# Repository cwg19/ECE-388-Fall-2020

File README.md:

# Function Generator
## UMassD ECE 388 Embedded System Design

### Project Scope
Simple Function gnerator
* produces sinusoid, square, and triangle waves
* Adjustable frequency up to 1MHz
* Adjustable gain between +/- ~10V
* Adjustable phase
* Rotary encoder w/ push button to select setting and change value
* Keypad to enter value
* LCD display

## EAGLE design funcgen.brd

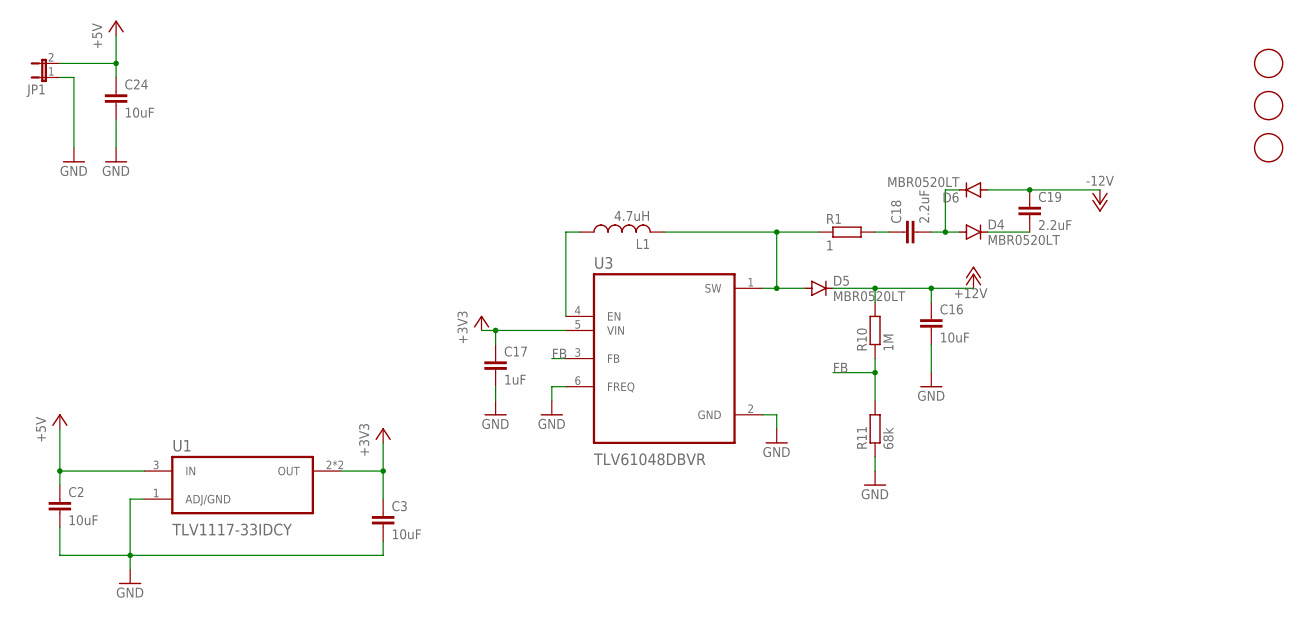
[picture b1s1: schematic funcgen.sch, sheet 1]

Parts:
C2, C3, C16, C24: 10uF; C0805
C17: 1uF; C0805
C18, C19: 2.2uF; C0805
D4, D5, D6: MBR0520LT; SOD123
JP1: JP1E; JP1
L1: 4.7uH; C0805
R1: 1; R0805
R10: 1M; R0805
R11: 68k; R0805
U1: TLV1117-33IDCY; SOT230P700X180-4N
U3: TLV61048DBVR; SOT95P280X145-6N
U$1, U$3, U$4: FIDUCIAL; FIDUCIAL_1MM

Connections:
+3V3: C3.1, C17.1, U1.2 (OUT), U1.4 (OUT), U3.5 (VIN); also elsewhere on the board
+5V: C2.1, C24.1, JP1.2, U1.3 (IN); also elsewhere on the board
+12V: C16.1, D5.C, R10.2; also elsewhere on the board
-12V: C19.1, D6.A; also elsewhere on the board
FB: R10.1, R11.2, U3.3 (FB)
GND: C2.2, C3.2, C16.2, C17.2, C24.2, JP1.1, R11.1, U1.1 (ADJ/GND), U3.2 (GND), U3.6 (FREQ); also elsewhere on the board
unnamed: L1.1, U3.4 (EN)
unnamed: D5.A, L1.2, R1.1, U3.1 (SW)
unnamed: C18.1, R1.2
unnamed: C18.2, D4.A, D6.C
unnamed: C19.2, D4.C

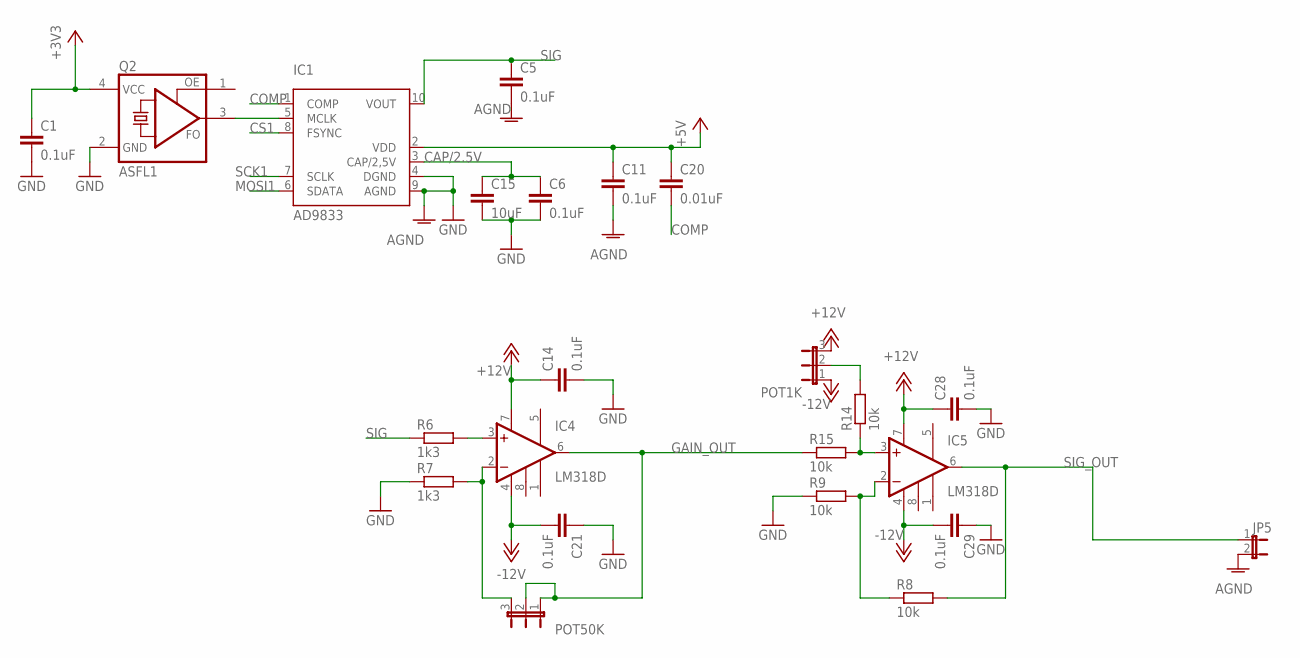
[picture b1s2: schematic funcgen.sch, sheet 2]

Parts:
C1, C5, C6, C11, C14, C21, C28, C29: 0.1uF; C0805
C15: 10uF; C0805
C20: 0.01uF; C0805
IC1: AD9833; MSOP10
IC4, IC5: LM318D; SOIC8
JP5: JP1E; JP1
POT1K, POT50K: JP2E; JP2
Q2: ASFL1; ASF
R6, R7: 1k3; R0805
R8, R9, R14, R15: 10k; R0805

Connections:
+3V3: C1.1, Q2.4 (VCC); also elsewhere on the board
+5V: C11.1, C20.1, IC1.2 (VDD); also elsewhere on the board
+12V: C14.1, C28.1, IC4.7 (V+), IC5.7 (V+), POT1K.3; also elsewhere on the board
-12V: C21.2, C29.2, IC4.4 (V-), IC5.4 (V-), POT1K.1; also elsewhere on the board
AGND: C5.2, C11.2, IC1.4 (DGND), IC1.9 (AGND), JP5.2
CAP/2.5V: C6.1, C15.1, IC1.3 (CAP/2,5V)
COMP: C20.2, IC1.1 (COMP)
CS1: IC1.8 (FSYNC); also elsewhere on the board
GAIN_OUT: IC4.6 (OUT), POT50K.1, POT50K.2, R15.1
GND: C1.2, C6.2, C14.2, C15.2, C21.1, C28.2, C29.1, Q2.2 (GND), R7.1, R9.1; also elsewhere on the board
MOSI1: IC1.6 (SDATA); also elsewhere on the board
unnamed: IC1.5 (MCLK), Q2.3 (FO)
unnamed: IC4.3 (+IN), R6.2
unnamed: IC4.2 (-IN), POT50K.3, R7.2
unnamed: IC5.3 (+IN), R14.1, R15.2
unnamed: POT1K.2, R14.2
unnamed: IC5.2 (-IN), R8.1, R9.2
SCK1: IC1.7 (SCLK); also elsewhere on the board
SIG: C5.1, IC1.10 (VOUT), R6.1
SIG_OUT: IC5.6 (OUT), JP5.1, R8.2

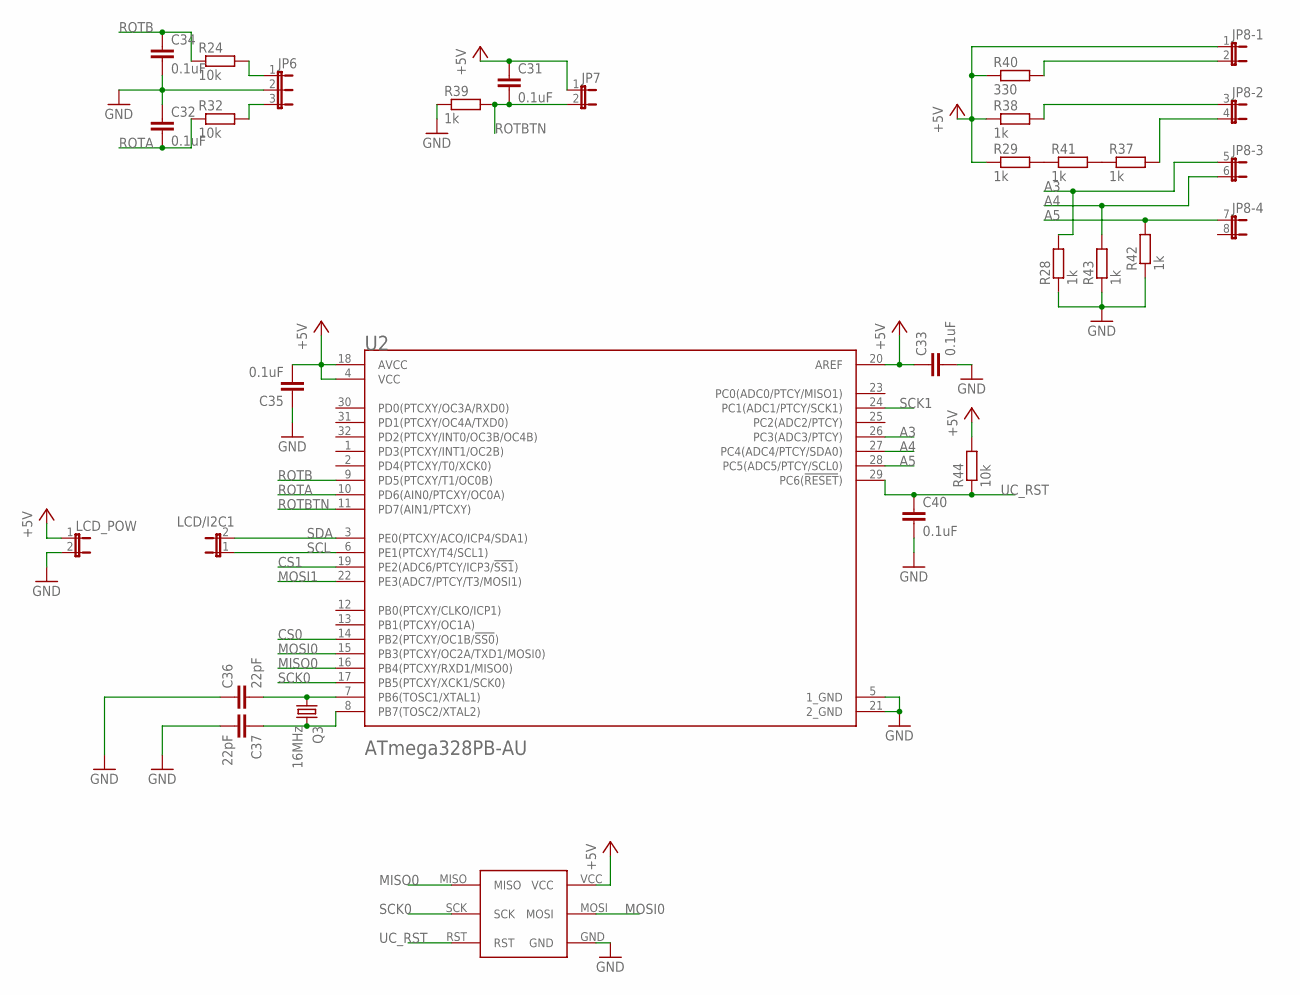
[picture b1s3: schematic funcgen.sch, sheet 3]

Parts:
C31, C32, C33, C34, C35, C40: 0.1uF; C0805
C36, C37: 22pF; C0805
JP6: JP2E; JP2
JP7: JP1E; JP1
JP8: JP4QE; JP4Q
LCD/I2C1: JP1E; JP1
LCD_POW: JP1E; JP1
Q3: 16MHz; HC49UP
R24, R32, R44: 10k; R0805
R28, R29, R37, R38, R39, R41, R42, R43: 1k; R0805
R40: 330; R0805
U2: MICROCHIP_ATMEGA328PB-AUMICROCHIP_ATMEGA328PB-AU_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; MICROCHIP_ATMEGA328PB-AU_0
U$2: AVR-ISP

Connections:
+5V: C31.1, C33.1, C35.2, JP7.1, JP8.1, LCD_POW.1, R29.1, R38.1, R40.1, R44.2, U2.4 (VCC), U2.18 (AVCC), U2.20 (AREF), U$2.VCC; also elsewhere on the board
A3: JP8.5 (1), R28.2, U2.26 (PC3(ADC3/PTCY))
A4: JP8.6 (2), R43.2, U2.27 (PC4(ADC4/PTCY/SDA0))
A5: JP8.7 (1), R42.2, U2.28 (PC5(ADC5/PTCY/SCL0))
CS0: U2.14 (PB2(PTCXY/OC1B/!SS0!))
CS1: U2.19 (PE2(ADC6/PTCY/ICP3/!SS1!)); also elsewhere on the board
GND: C32.1, C33.2, C34.2, C35.1, C36.1, C37.2, C40.2, JP6.2, LCD_POW.2, R28.1, R39.1, R42.1, R43.1, U2.5 (1_GND), U2.21 (2_GND), U$2.GND; also elsewhere on the board
MISO0: U2.16 (PB4(PTCXY/RXD1/MISO0)), U$2.MISO
MOSI0: U2.15 (PB3(PTCXY/OC2A/TXD1/MOSI0)), U$2.MOSI
MOSI1: U2.22 (PE3(ADC7/PTCY/T3/MOSI1)); also elsewhere on the board
unnamed: JP6.1, R24.2
unnamed: JP6.3, R32.2
unnamed: C36.2, Q3.1, U2.7 (PB6(TOSC1/XTAL1))
unnamed: C37.1, Q3.2, U2.8 (PB7(TOSC2/XTAL2))
unnamed: R37.1, R41.2
unnamed: R29.2, R41.1
unnamed: JP8.2, R40.2
unnamed: JP8.3 (1), R38.2
unnamed: JP8.4 (2), R37.2
ROTA: C32.2, R32.1, U2.10 (PD6(AIN0/PTCXY/OC0A))
ROTB: C34.1, R24.1, U2.9 (PD5(PTCXY/T1/OC0B))
ROTBTN: C31.2, JP7.2, R39.2, U2.11 (PD7(AIN1/PTCXY))
SCK0: U2.17 (PB5(PTCXY/XCK1/SCK0)), U$2.SCK
SCK1: U2.24 (PC1(ADC1/PTCY/SCK1)); also elsewhere on the board
SCL: LCD/I2C1.1, U2.6 (PE1(PTCXY/T4/SCL1))
SDA: LCD/I2C1.2, U2.3 (PE0(PTCXY/ACO/ICP4/SDA1))
UC_RST: C40.1, R44.1, U2.29 (PC6(!RESET!)), U$2.RST

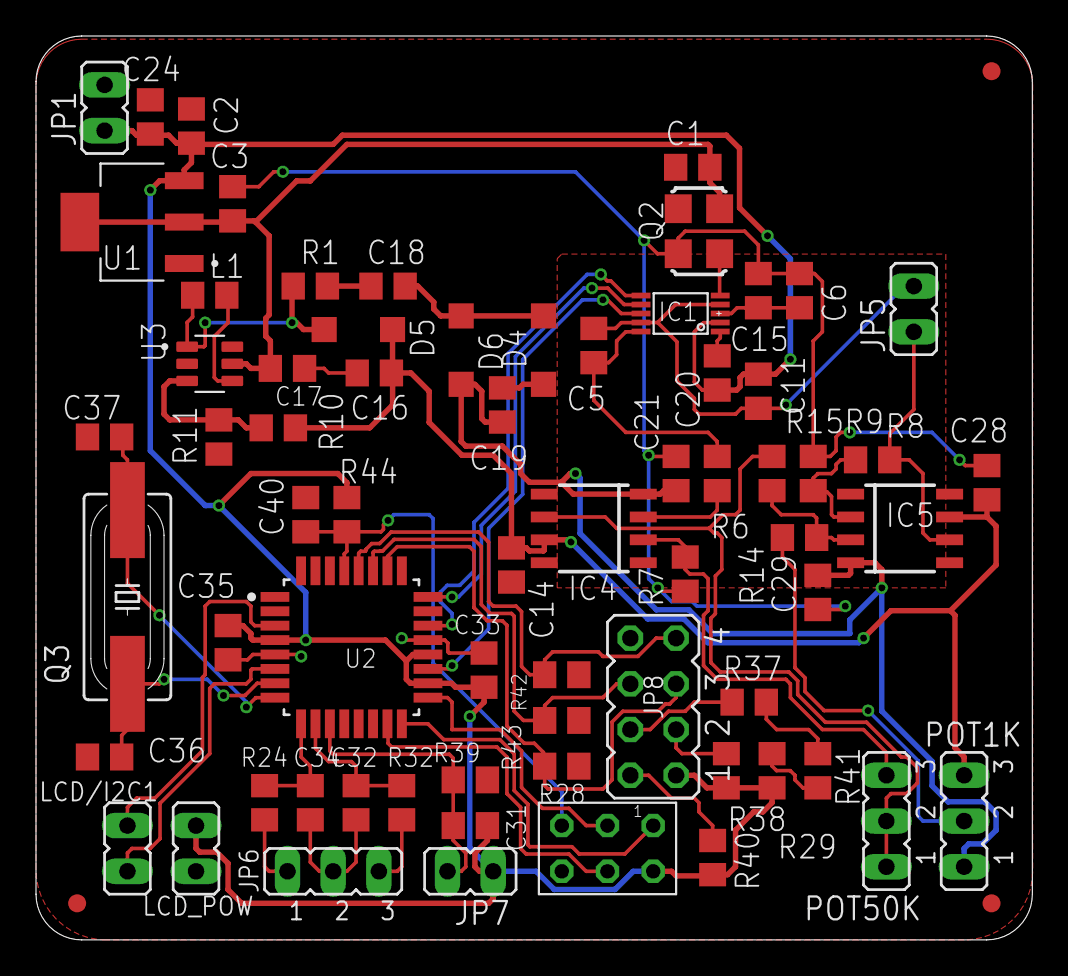
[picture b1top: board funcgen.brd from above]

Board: 2 copper layers, 55.4 x 50.2 mm, 71 parts (0 on the bottom side), 47 nets.

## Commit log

2020-10-11 Initial software upload
2020-10-11 Bill of Materials
    Revised Bill of Materials submission with information on parts from LCSC and digikey depending on availability.
    I left resistors and capacitors blank except for the component value because we are all supposed to be using the 0805 components. I did not fill out LEDs because I do not need any particular LEDs. Co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
2020-10-12 Updating UI solution
    Rotary encoder interfacing is successful. Have yet to separate functionality into header and implementation files for lcd and rotary encoder functionality. The main program of this project is a test,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
2020-10-12 Functional user Interface program
    UI code with 4x20 LCD and I2C backpack. Works well despite sometimes skipping modes when rotating encoder and sometimes missing button pushes. I tried incorporating a timer to check the push button a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
2020-10-12 .csv BOM
2020-10-13 Create BOM\
2020-10-13 Bill of materials folder
    sdfljnsdlfnsdf
2020-10-13 bill of materials
2020-10-13 AD9833 test program
    Added / adjusted some code to the AD9833 lib I found online. UNTESTED. I need to wait until lab on Wednesday / Thursday in order to use the digilent / oscilloscope to monitor the output of the functi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
2020-10-14 datasheets
    datasheets
2020-10-14 Testing Signal Generator
    Able to change frequency and mode. Need to clean up / modularize code and continue testing
2020-10-17 BOM iteration 2 the sequel
2020-10-17 Modularized AD9833 Header and Implementation
    Refined the .h and .c file for AD9833 for my purposes. CURRENTLY UNTESTED. Need to test this solution with oscilloscope / logic analyzer when I have lab time on Wednesday. The solution builds, but wh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
2020-10-18 BOM v3: the BOMbest BOM to Date
    Here we go again
2020-10-18 BOM again
    idk
2020-10-21 Integrating AD9833 and UI
    Integrating AD99833 signal generator with user interface code. UNTESTED. This will probably do something I just don't know what or how well. It wasn't too much additional stuffs to the UI, just trigg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
2020-10-23 Clean up
    Too many globals. Stuff wasn't working when tested in lab. Still need to debug what is actually going on with the code and why it isnt working like I want next time i have access to an oscilloscope. 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
2020-10-24 Further refactoring
    Completely untested... probably a terrible idea. Going to test actual functionality now. Functionally, this code should be same, however something wasn't working prior. I tried making small alteratio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
2020-10-27 Functional prototype code
    This program is tested with the the Digilent oscilloscope feature. It effectively changes the frequency, phase and signal shape of the AD9833 via the user interface (rotary encoder). I am realizing t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
2020-11-03 Schematic and Board pics
    Images of first-cut schematic and board layout with and without ratsnest view.
2020-11-03 Uploading CAM for 1st cut board
    1st cut board design CAMOutput files. The dimensions of my board are too large and that is the first thing I need to change. There were 2 warning on my schematic which were related to AGND being conn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
2020-11-08 Eagle schematic and board directory
    Keep Schematic and Board under version control
2020-11-08 Eagle board and schematic files
2020-11-09 Rename funcgen1.brd to funcgen.brd
2020-11-09 Rename funcgen1.sch to funcgen.sch
2020-11-09 Revised and Updated Schematic and Board
    Changed schematic to multiple sheets with better organization. Board layout is redone entirely. Surface area is nearly cut in half from first design.
    ISSUES: 1) need to verify / find the proper DC jack connector.
    2) need an 0805 inductor package. I believe I left enough space for it, but for now the footprint is entirely incorrect
2020-11-09 Uploading Schematic Image
    Schematic Printed to PDF. Multiple sheets and improved organization
2020-11-09 Upload Revised Board Images
    PCB Layout Images with and without ratsnest view
2020-11-09 CAM files used for project
2020-11-09 Gerber and Assembly File Upload
2020-11-09 Just the Gerbers
2020-11-12 Function Generator pdfs upload
2020-11-12 Eagle Schematic and Board Upload
    Current Board and Schematic
2020-11-12 Re-upload board and schematic
2020-11-12 Updated Gerber and Assembly FIles
2020-11-12 Updated Board and Schematic
    Updated Board and Schematic with SMA Schottky diodes and ISP pin 1 marking
2020-11-12 Updated Board and Schematic Gerbs and stuffs
    Updated images for schematic and layout. SMA schottky diodes placed; NOTE: the Schottky diode symbol on the schematic looks like a normal diode, however the description claims it is a Schottky barrie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
2020-11-20 assembly BOM
